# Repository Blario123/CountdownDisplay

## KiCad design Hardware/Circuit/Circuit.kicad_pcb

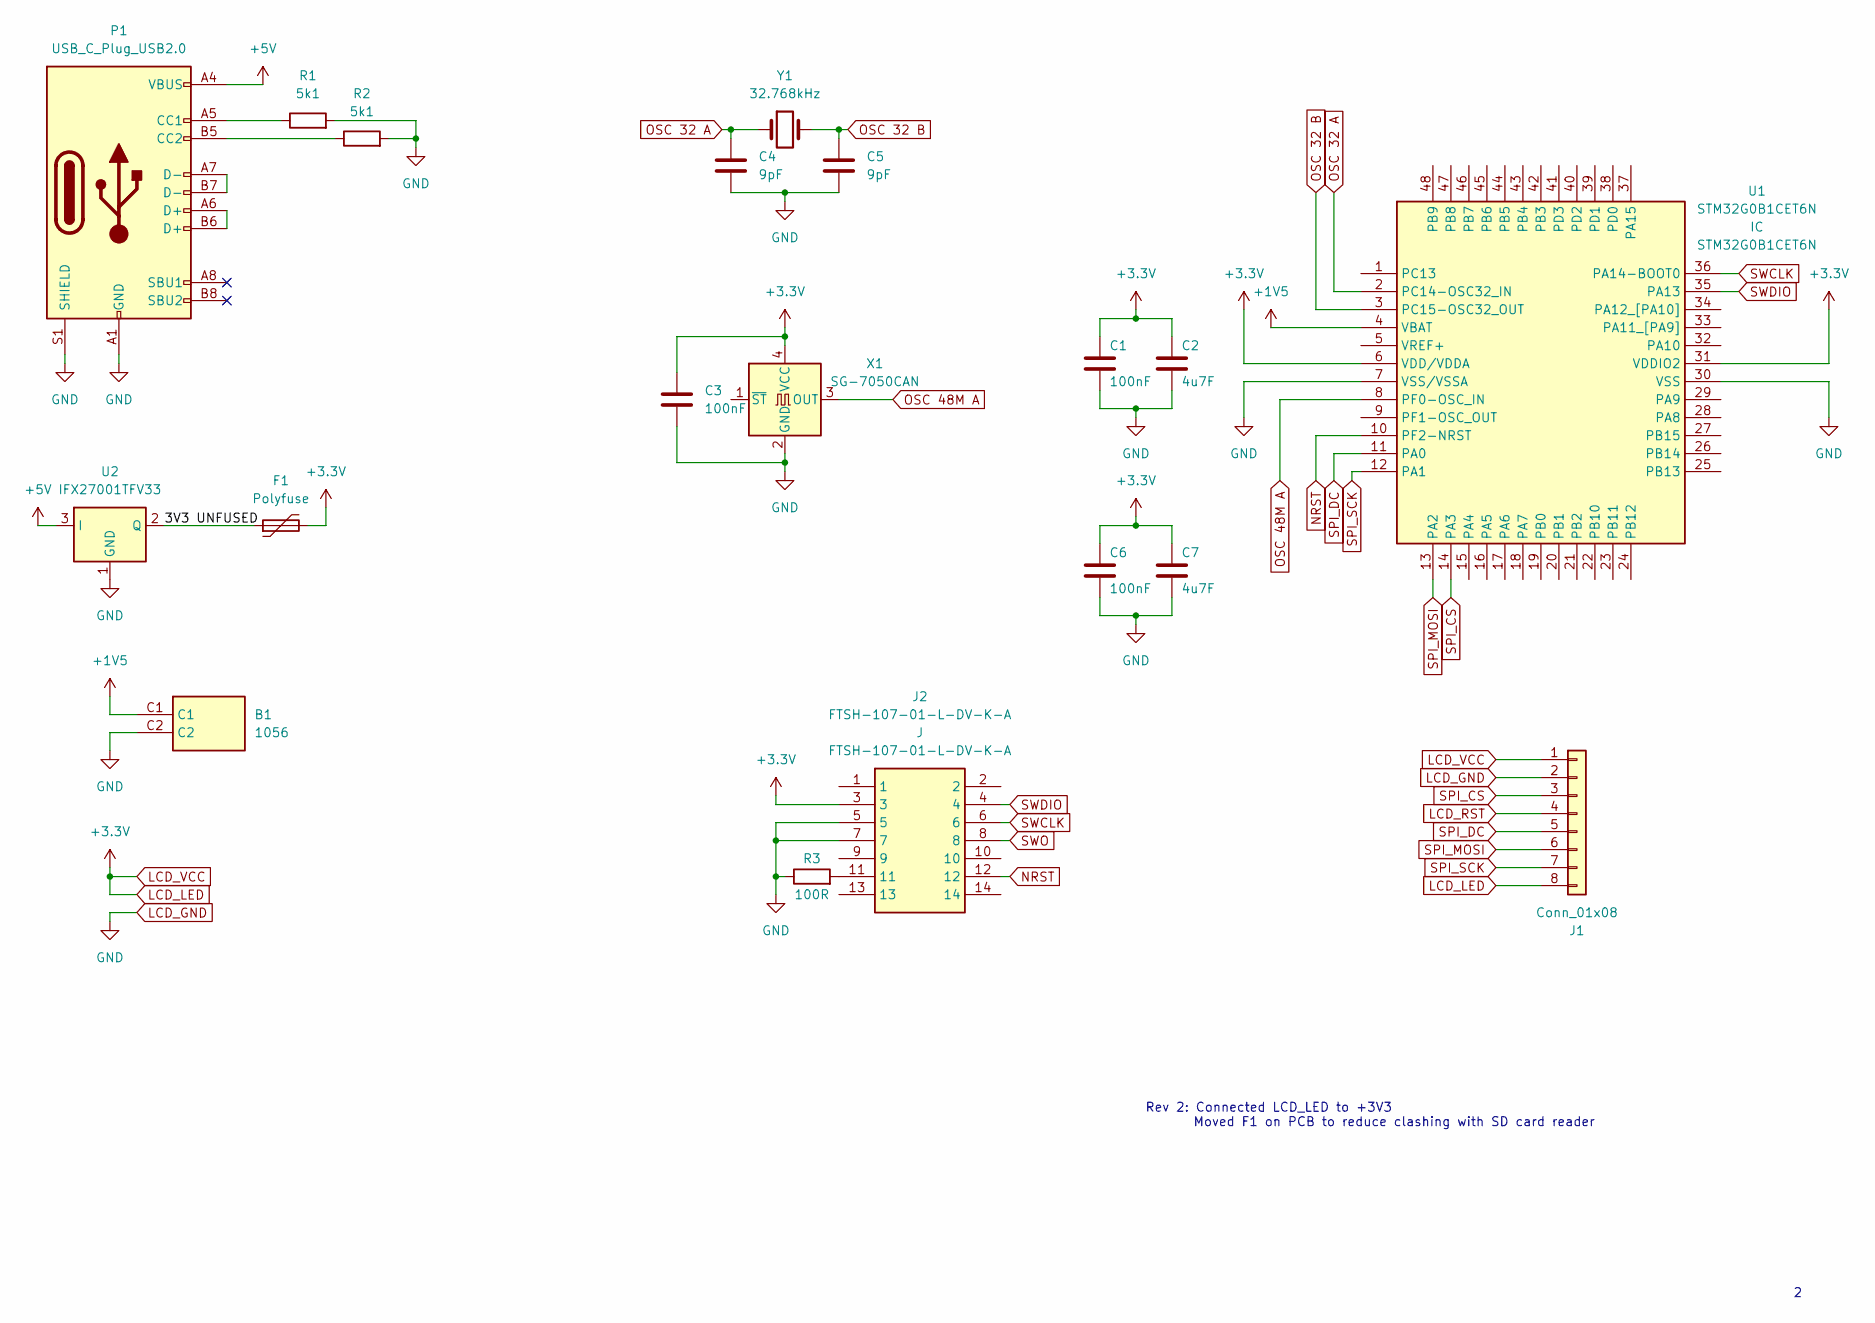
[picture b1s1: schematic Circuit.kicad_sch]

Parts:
B1: 1056; Manufacturer_Part_Number 1056; Mouser Part Number 534-1056
C1, C3, C6: 100nF; C_0805_2012Metric
C2, C7: 4u7F; C_0805_2012Metric
C4, C5: 9pF; C_0805_2012Metric
F1: Polyfuse; Fuse_Bourns_MF-RG300
J1: Conn_01x08; PinSocket_1x08_P2.54mm_Vertical
J2: FTSH-107-01-L-DV-K-A; FTSH-107-XX-YYY-DV-K-A; Manufacturer_Part_Number FTSH-107-01-L-DV-K-A; Mouser Part Number 200-FTSH10701LDVKA
P1: USB_C_Plug_USB2.0; USB_C_Receptacle_GCT_USB4085
R1, R2: 5k1; R_0805_2012Metric
R3: 100R; R_0805_2012Metric
U1: STM32G0B1CET6N; LQFP-48_7x7mm_P0.5mm; Manufacturer_Part_Number STM32G0B1CET6N; Mouser Part Number 511-STM32G0B1CET6N
U2: IFX27001TFV33; TO-252-3_TabPin2
X1: SG-7050CAN; Oscillator_SMD_SeikoEpson_SG8002CA-4Pin_7.0x5.0mm
Y1: 32.768kHz; Crystal_SMD_3215-2Pin_3.2x1.5mm

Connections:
+1V5: B1.C1, U1.4 (VBAT)
+5V: P1.A4 (VBUS), P1.A9 (VBUS), P1.B4 (VBUS), P1.B9 (VBUS), U2.3 (I)
/3V3 UNFUSED: F1.1, U2.2 (Q)
LCD_GND: B1.C2, C1.2, C2.2, C3.2, C4.2, C5.2, C6.2, C7.2, J1.2, J2.5, J2.7, P1.A1 (GND), P1.A12 (GND), P1.B1 (GND), P1.B12 (GND), P1.S1 (SHIELD), R1.2, R2.2, R3.1, U1.7 (VSS/VSSA), U1.30 (VSS), U2.1 (GND), X1.2 (GND)
LCD_LED: C1.1, C2.1, C3.1, C6.1, C7.1, F1.2, J1.1, J1.8, J2.3, U1.6 (VDD/VDDA), U1.31 (VDDIO2), X1.4 (VCC)
LCD_RST: J1.4
NRST: J2.12, U1.10 (PF2-NRST)
unnamed: J2.11, R3.2
unnamed: P1.A5 (CC1), R1.1
unnamed: P1.A6 (D+), P1.B6 (D+)
unnamed: P1.A7 (D-), P1.B7 (D-)
unnamed: P1.B5 (CC2), R2.1
OSC 32 A: C4.1, U1.2 (PC14-OSC32_IN), Y1.1
OSC 32 B: C5.1, U1.3 (PC15-OSC32_OUT), Y1.2
OSC 48M A: U1.8 (PF0-OSC_IN), X1.3 (OUT)
SPI_CS: J1.3, U1.14 (PA3)
SPI_DC: J1.5, U1.11 (PA0)
SPI_MOSI: J1.6, U1.13 (PA2)
SPI_SCK: J1.7, U1.12 (PA1)
SWCLK: J2.6, U1.36 (PA14-BOOT0)
SWDIO: J2.4, U1.35 (PA13)
SWO: J2.8

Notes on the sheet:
Rev 2: Connected LCD_LED to +3V3 Moved F1 on PCB to reduce clashing with SD card reader

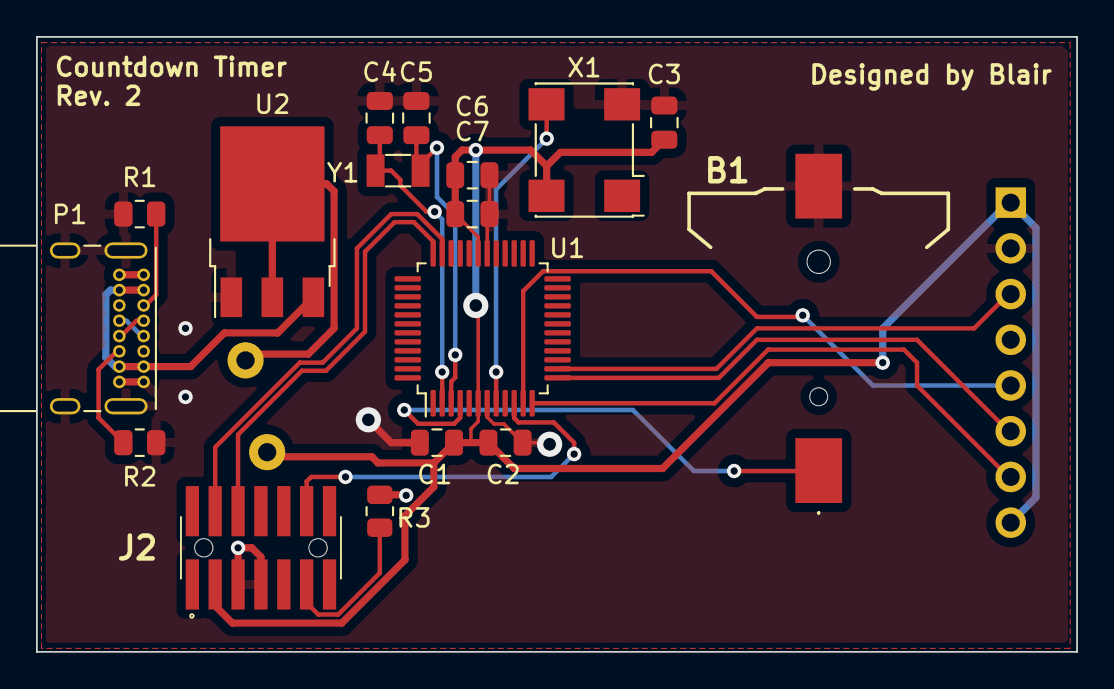
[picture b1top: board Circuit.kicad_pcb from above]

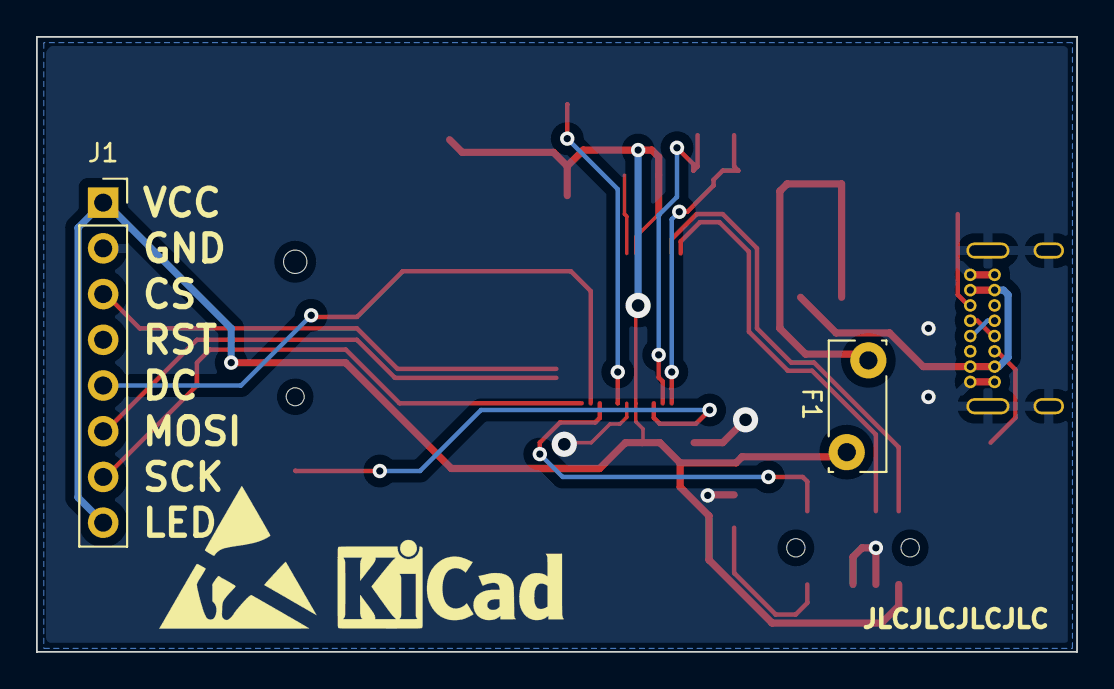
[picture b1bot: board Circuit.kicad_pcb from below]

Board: 2 copper layers, 57.8 x 34.2 mm, 19 parts (2 on the bottom side), 20 nets.

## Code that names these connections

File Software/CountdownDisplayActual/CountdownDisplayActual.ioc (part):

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Mcu.Name=STM32G0B1C(B-C-E)TxN
Mcu.Package=LQFP48
Mcu.UserName=STM32G0B1CETxN
PA0.GPIOParameters=GPIO_Speed,GPIO_PuPd,GPIO_Label
PA0.GPIO_Label=SPI_DC
PA0.GPIO_PuPd=GPIO_NOPULL
PA0.GPIO_Speed=GPIO_SPEED_FREQ_LOW
PA0.Signal=GPIO_Output
PA1.Mode=Full_Duplex_Master
PA1.Signal=SPI1_SCK
PA13.Mode=Serial_Wire
PA13.Signal=SYS_SWDIO
PA14-BOOT0.Mode=Serial_Wire
PA14-BOOT0.Signal=SYS_SWCLK
PA2.Mode=Full_Duplex_Master
PA2.Signal=SPI1_MOSI
PA3.GPIOParameters=GPIO_Speed,GPIO_PuPd,GPIO_Label
PA3.GPIO_Label=SPI_CS
PA3.GPIO_PuPd=GPIO_NOPULL
PA3.GPIO_Speed=GPIO_SPEED_FREQ_LOW
PA3.Signal=GPIO_Output
PA6.Mode=Full_Duplex_Master
PA6.Signal=SPI1_MISO
PF0-OSC_IN\ (PF0).Mode=HSE-External-Clock-Source
PF0-OSC_IN\ (PF0).Signal=RCC_OSC_IN
RCC.HSE_VALUE=48000000
RCC.SYSCLKFreq_VALUE=48000000
RCC.SYSCLKSource=RCC_SYSCLKSOURCE_HSE
board=custom

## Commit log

2024-10-17 Initial Commit
    Software: Not finished
    Hardware: Rev 2
2024-10-29 Tinkering with clock sources
    It is suspected that the clock source is not working, thus the SPI will not control the display.
    Also removed the debug/release build directories generated by STM32CubeIDE
2024-10-29 Updated .gitignore
    Forgot the release directory
2024-10-30 Added centered text
    The addText function now properly directs to enabling the x-offset if using centered text or not.
    Also added the examples directory for PoC code to do with the main STM code.
2024-10-30 Removed .settings directory from CountdownDisplayDev
2024-10-30 Semi-working text rendering
    Weird behaviour of the board, but occasionally the text will properly render. Possible electrical issue.
2024-10-31 Missing HAL_SPI_Abort()
    The reason behind the display not updating was due to the fact that the SPI bus had not been aborted after a transmission and moving onto the next.
    Also adding in date/time calculations
